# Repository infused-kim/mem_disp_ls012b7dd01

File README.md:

# Sharp Memory Display Breakout Board for LS012B7DD01

The purpose of this board is to provide a near-drop-in low-power display replacement for the popular SSD1306 128x32 OLED.

It is meant to be used in wireless ergo split keyboards such as the [sofle](https://github.com/josefadamcik/SofleKeyboard) and [corne](https://github.com/foostan/crkbd).

> :warning: **Warning:**
>
> This board has not been tested yet.

## Credits

- Crehmann and [his breakout board for LS011B7DH03](https://github.com/crehmann/Sharp-Memory-LCD-Breakout), which I used as a reference and from which I drew a lot of inspiration
- Jon808517 [and his board](https://discord.com/channels/719497620560543766/785533287049330729/964635218940141569), which lead me to pursue this project
- All of the super helpful guys on the ZMK discord who patiently answered all my questions

## Related Projects

- [crehmann/Sharp-Memory-LCD-Breakout](https://github.com/crehmann/Sharp-Memory-LCD-Breakout)
- [karnadii/sharp_memory_display_breakout](https://github.com/karnadii/sharp_memory_display_breakout)
- [adafruit/Adafruit-Sharp-Memory-Display-PCBs](https://github.com/adafruit/Adafruit-Sharp-Memory-Display-PCBs)

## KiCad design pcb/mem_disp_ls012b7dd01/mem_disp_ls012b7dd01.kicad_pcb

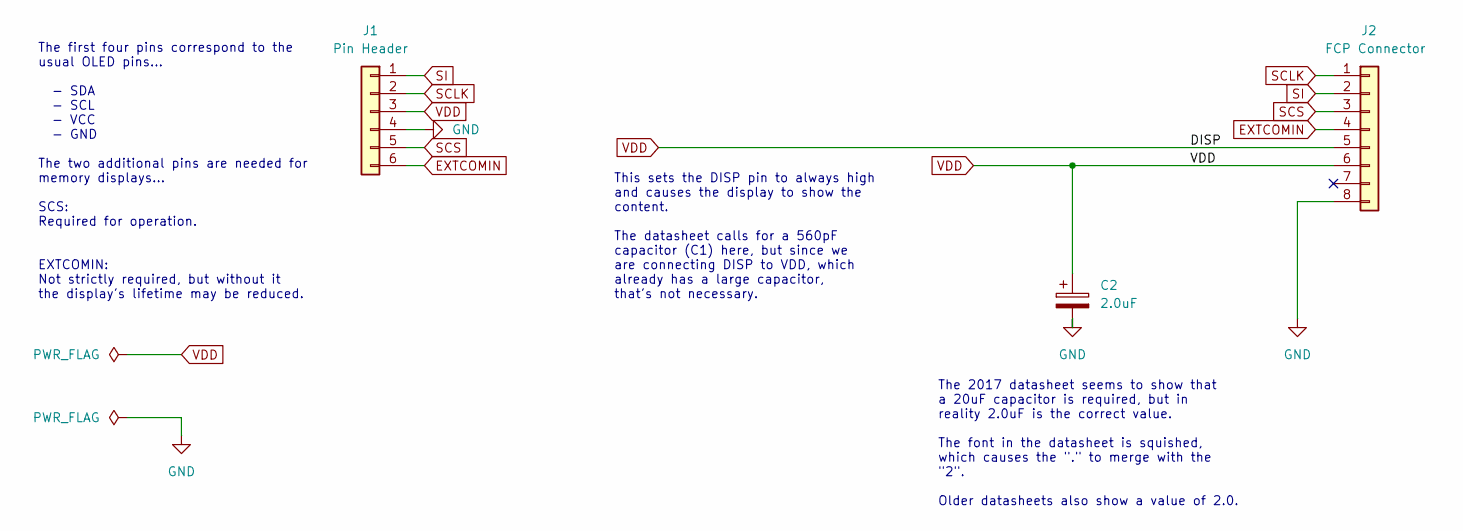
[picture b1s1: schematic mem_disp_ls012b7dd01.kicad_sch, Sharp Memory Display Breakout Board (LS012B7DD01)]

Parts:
C2: 2.0uF; C_0603_1608Metric_Pad1.08x0.95mm_HandSolder
J1: Pin Header; PinSocket_1x04_1x02_P2.54mm_Vertical
J2: FCP Connector; Hirose_FH12-8S-0.5SH_1x08-1MP_P0.50mm_Horizontal

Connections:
EXTCOMIN: J1.6, J2.4
GND: C2.2, J1.4, J2.8
SCLK: J1.2, J2.1
SCS: J1.5, J2.3
SI: J1.1, J2.2
VDD: C2.1, J1.3, J2.5, J2.6

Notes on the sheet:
The 2017 datasheet seems to show that a 20uF capacitor is required, but in reality 2.0uF is the correct value. The font in the datasheet is squished, which causes the "." to merge with the "2". Older datasheets also show a value of 2.0.
The first four pins correspond to the usual OLED pins... - SDA - SCL - VCC - GND The two additional pins are needed for memory displays... SCS: Required for operation. EXTCOMIN: Not strictly required, but without it the display's lifetime may be reduced.
This sets the DISP pin to always high and causes the display to show the content. The datasheet calls for a 560pF capacitor (C1) here, but since we are connecting DISP to VDD, which already has a large capacitor, that's not necessary.

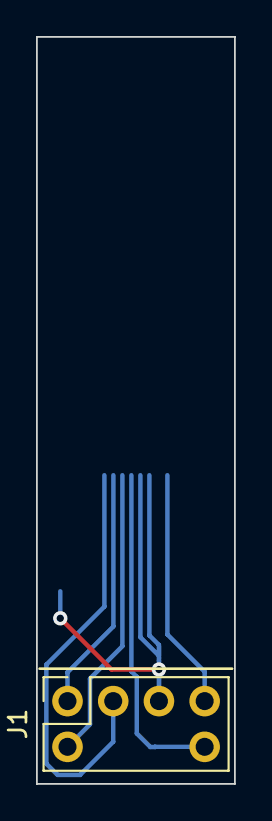
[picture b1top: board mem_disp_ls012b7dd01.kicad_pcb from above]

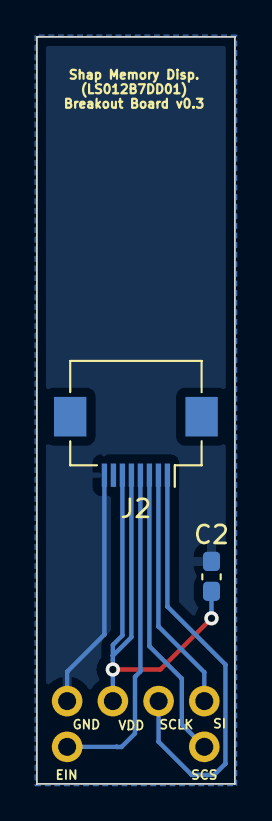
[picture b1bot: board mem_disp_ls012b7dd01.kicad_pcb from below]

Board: 2 copper layers, 11.0 x 41.5 mm, 3 parts (2 on the bottom side), 6 nets.

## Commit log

2022-04-25 Added initial version
2022-04-25 Fixed capacitor mix up
    VDD pin was connected to DISP capacitor and DISP capacitor was connected to VDD.
    From an electrical perspective it didn’t matter though.
2022-04-26 Fixed C1 capacity from 20uF to 2.0uF
    The 2017 datasheet seems to show that a 20uF capacitor is requiered, but in reality 2.0uF is the correct value.
    The font in the datasheet is squished, which causes the "." to merge with the
    "2".
    Older datasheets also show a value of 2.0.
2022-04-26 Added README to gerbers directory
2022-04-26 Moved FPC connector up a little
2022-04-26 Removed DISP C1 capacitor
    The datasheet calls for a 560pF capacitor (C1) connected to DISP, but since we are connecting DISP to VDD, which already has a large capacitor, that's not necessary.
